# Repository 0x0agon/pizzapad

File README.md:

# pizzapad

## What is pizzapad?
pizzapad is a 5 key macropad with encoder and rgb led support inspired by Stellar Pizza's flaming pizza logo!

## How can I build one?
### Create the PCB
The latest gerbers files are included in the "gerber" folder. These can be used to order pcb's from your favorite pcb manufacturer, such as [JLCPCB](https://jlcpcb.com/)

### Buy and Solder parts

To build a pizzapad you'll need

|Part|Quantity|Digikey #|Manufactuer #|
|---|---|---|---|
|Pcb|1|N/A|N/A|
|cherryMX compatible switches|5|N/A|N/A|
|cherryMX compatible hotswap sockets|5|N/A|N/A|
|promicro compatible microcontroller|1|N/A|N/A|
|reset switch|1|B3U-1000P|SW1020CT-ND|
|rotary encoder|1|PEC11R-4215F-S0024|PEC11R-4215F-S0024-ND|
|addressable led|5|4684|1528-4684-ND|
|diode|5|1N4148WX-TP|1N4148WX-TPMSCT-ND|
|10K ohm resistor|2|RMCF0805JT10k0|RMCF0805JT10k0CT-ND|

### Install firmware
pizzapad's firmware is based on The [QMK Project](https://github.com/qmk/qmk_firmware)

1) Download the base QMK firmware following the instructions on QMK's github page
2) Create a folder called `pizzapad` in `qmk_firmware/keyboards`
3) Build the firmware according to QMK's build instructions, pointing it to the `pizzapad` keyboard folder.
4) Profit!

#### Default key layout
  
The default has 4 layers.  
Switch layers by pressing the encoder in.
##### Layer 1 - Media [Gold]
This layer focuses on media controls, with the encoder controlling volume

##### Layer 2 - FN [Red]
This layer focuses on some hopefully useful shortcuts. The encoder switches between active windows (simulates alt-tab)

##### Layer 3 - Scroll [Magenta]
This layer brings scrolling to the macropad. The encoder controls scrolling vertically, and buttons 4 + 5 control horizontal scrolling

##### Layer 4 - RGB [Teal]
This layer controls the rgb indicator lights. The encoder turns brightness up and down. This layer isn't fully functional yet, but brightness controls should work.

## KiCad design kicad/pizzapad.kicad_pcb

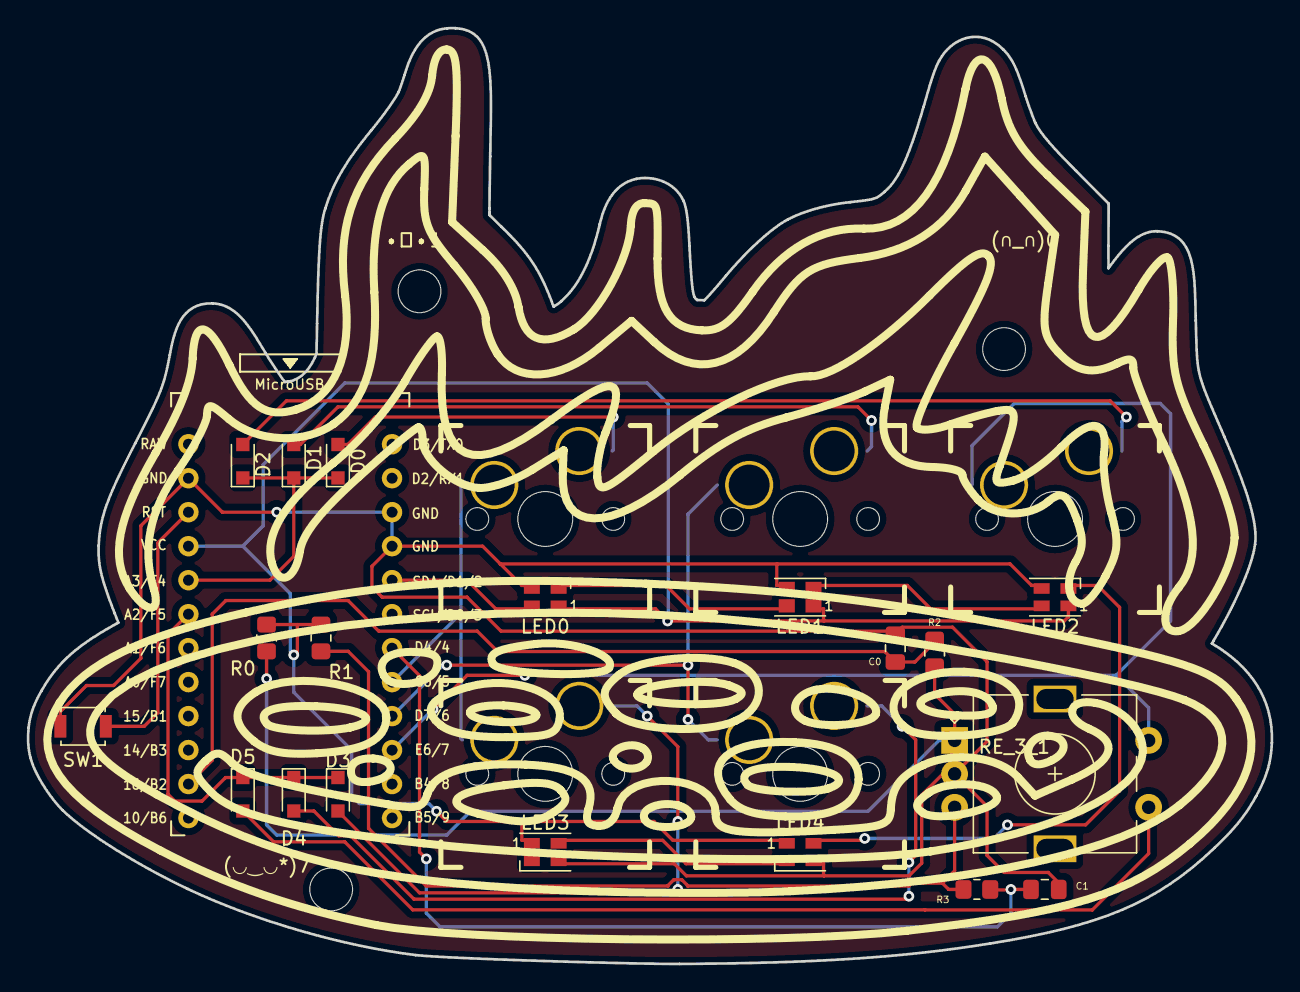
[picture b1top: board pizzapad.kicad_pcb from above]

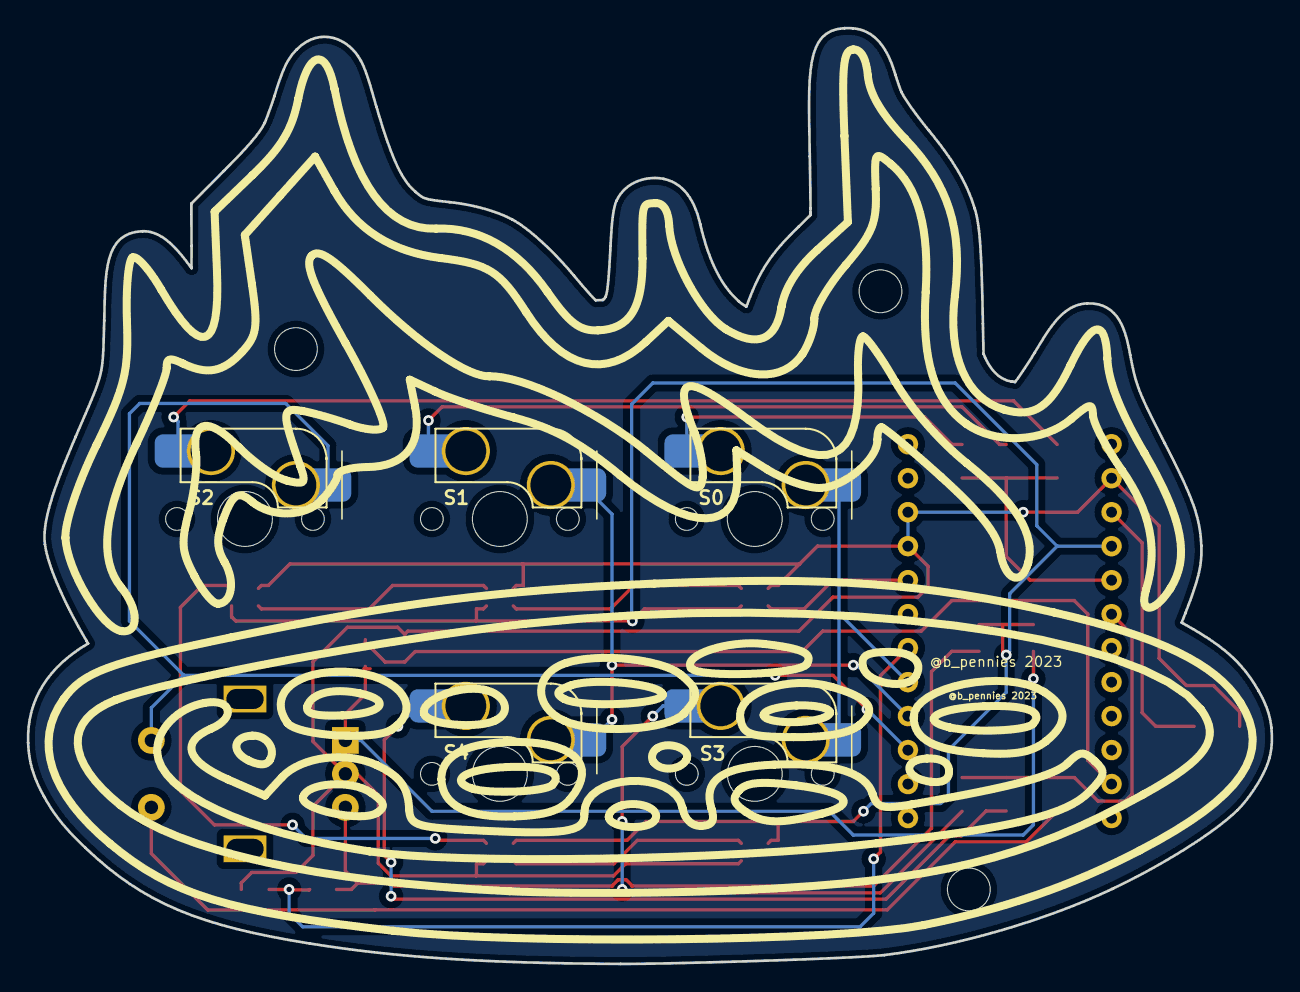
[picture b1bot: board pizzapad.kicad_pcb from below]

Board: 2 copper layers, 93.0 x 69.9 mm, 28 parts (5 on the bottom side), 23 nets.

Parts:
(∩_∩)0: _; MountingHole_3.2mm_M3_ISO7380
(◡‿◡*)7: _; MountingHole_3.2mm_M3_ISO7380
B1: SPARKFUN_PRO_MICRO; ProMicro_v3.5
C0, C1: Filter C0.01uF; C_0805_2012Metric_Pad1.18x1.45mm_HandSolder
D0, D1, D2, D3, D4, D5: 1N4148WT; D_SOD-323_HandSoldering
LED0, LED1, LED2, LED3, LED4: SK6812MINI_1; LED_SK6805_PLCC4_2.4x2.7mm_P1.3mm
R0, R1: Pull up R10k; R_0805_2012Metric_Pad1.20x1.40mm_HandSolder
R2, R3: Filter R10k; R_0805_2012Metric_Pad1.20x1.40mm_HandSolder
RE_3_1: Encoder; RotaryEncoder_Alps_EC11E-Switch_Vertical_H20mm
S0, S1, S2, S3, S4: Cherry MX Switch; Kailh-CPG151101S11_MX_Socket-1.00u
SW1: SW_SPST; SW_SPST_B3U-1000P
•ᴥ•1: _; MountingHole_3.2mm_M3_ISO7380

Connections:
/COL0: B1.8 (*5), S0.S2 (2), S3.S2 (2)
/COL1: B1.9 (*6), S1.S2 (2), S4.S2 (2)
/COL2: B1.10 (7), RE_3_1.S2 (2), S2.S2 (2)
/ENCODER0_L0: B1.14 (11(MOSI)), C0.2, R2.1
/ENCODER0_L1: B1.7 (4), C1.2, R3.2
/KEY_LEDS: B1.5 (2), LED0.4 (DIN)
/RESET: B1.22 (RESET), SW1.1 (A)
/ROW0: B1.20 (A3), D0.1 (K), D1.1 (K), D2.1 (K)
/ROW1: B1.19 (A2), D3.1 (K), D4.1 (K), D5.1 (K)
GND: B1.3 (GND@1), B1.4 (GND), B1.23 (GND@2), C0.1, C1.1, LED0.3 (VSS), LED1.3 (VSS), LED2.3 (VSS), LED3.3 (VSS), LED4.3 (VSS), RE_3_1.C, SW1.2 (B)
unnamed: D0.2 (A), S0.S1 (1)
unnamed: D1.2 (A), S1.S1 (1)
unnamed: D2.2 (A), S2.S1 (1)
unnamed: D3.2 (A), S3.S1 (1)
unnamed: D4.2 (A), S4.S1 (1)
unnamed: D5.2 (A), RE_3_1.S1 (1)
unnamed: LED0.2 (DOUT), LED1.4 (DIN)
unnamed: LED1.2 (DOUT), LED2.4 (DIN)
unnamed: LED2.2 (DOUT), LED4.4 (DIN)
unnamed: LED3.4 (DIN), LED4.2 (DOUT)
unnamed: R0.2, R2.2, RE_3_1.A
unnamed: R1.1, R3.1, RE_3_1.B
VCC: B1.21 (VCC), LED0.1 (VDD), LED1.1 (VDD), LED2.1 (VDD), LED3.1 (VDD), LED4.1 (VDD), R0.1, R1.2

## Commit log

2023-10-09 Initial commit of V2 pizzapad and v1 pizzapad-base
2024-04-05 restructuring repo, cleaning up
2024-04-08 Update rgb to change on layer switch
2024-04-15 Updated keymap
2024-04-22 Updating readme
2024-04-22 Add line breaks to README
2024-04-22 Add layer colors to README
